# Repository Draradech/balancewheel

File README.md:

# Balance Wheel (Rev. 2)

This repository will grow over time to include everything you need to build your own balance wheel: 
https://hackaday.io/project/4267-balance-wheel

This includes circuit board design, partslist, drawings to lasercut HDF parts and build instructions.

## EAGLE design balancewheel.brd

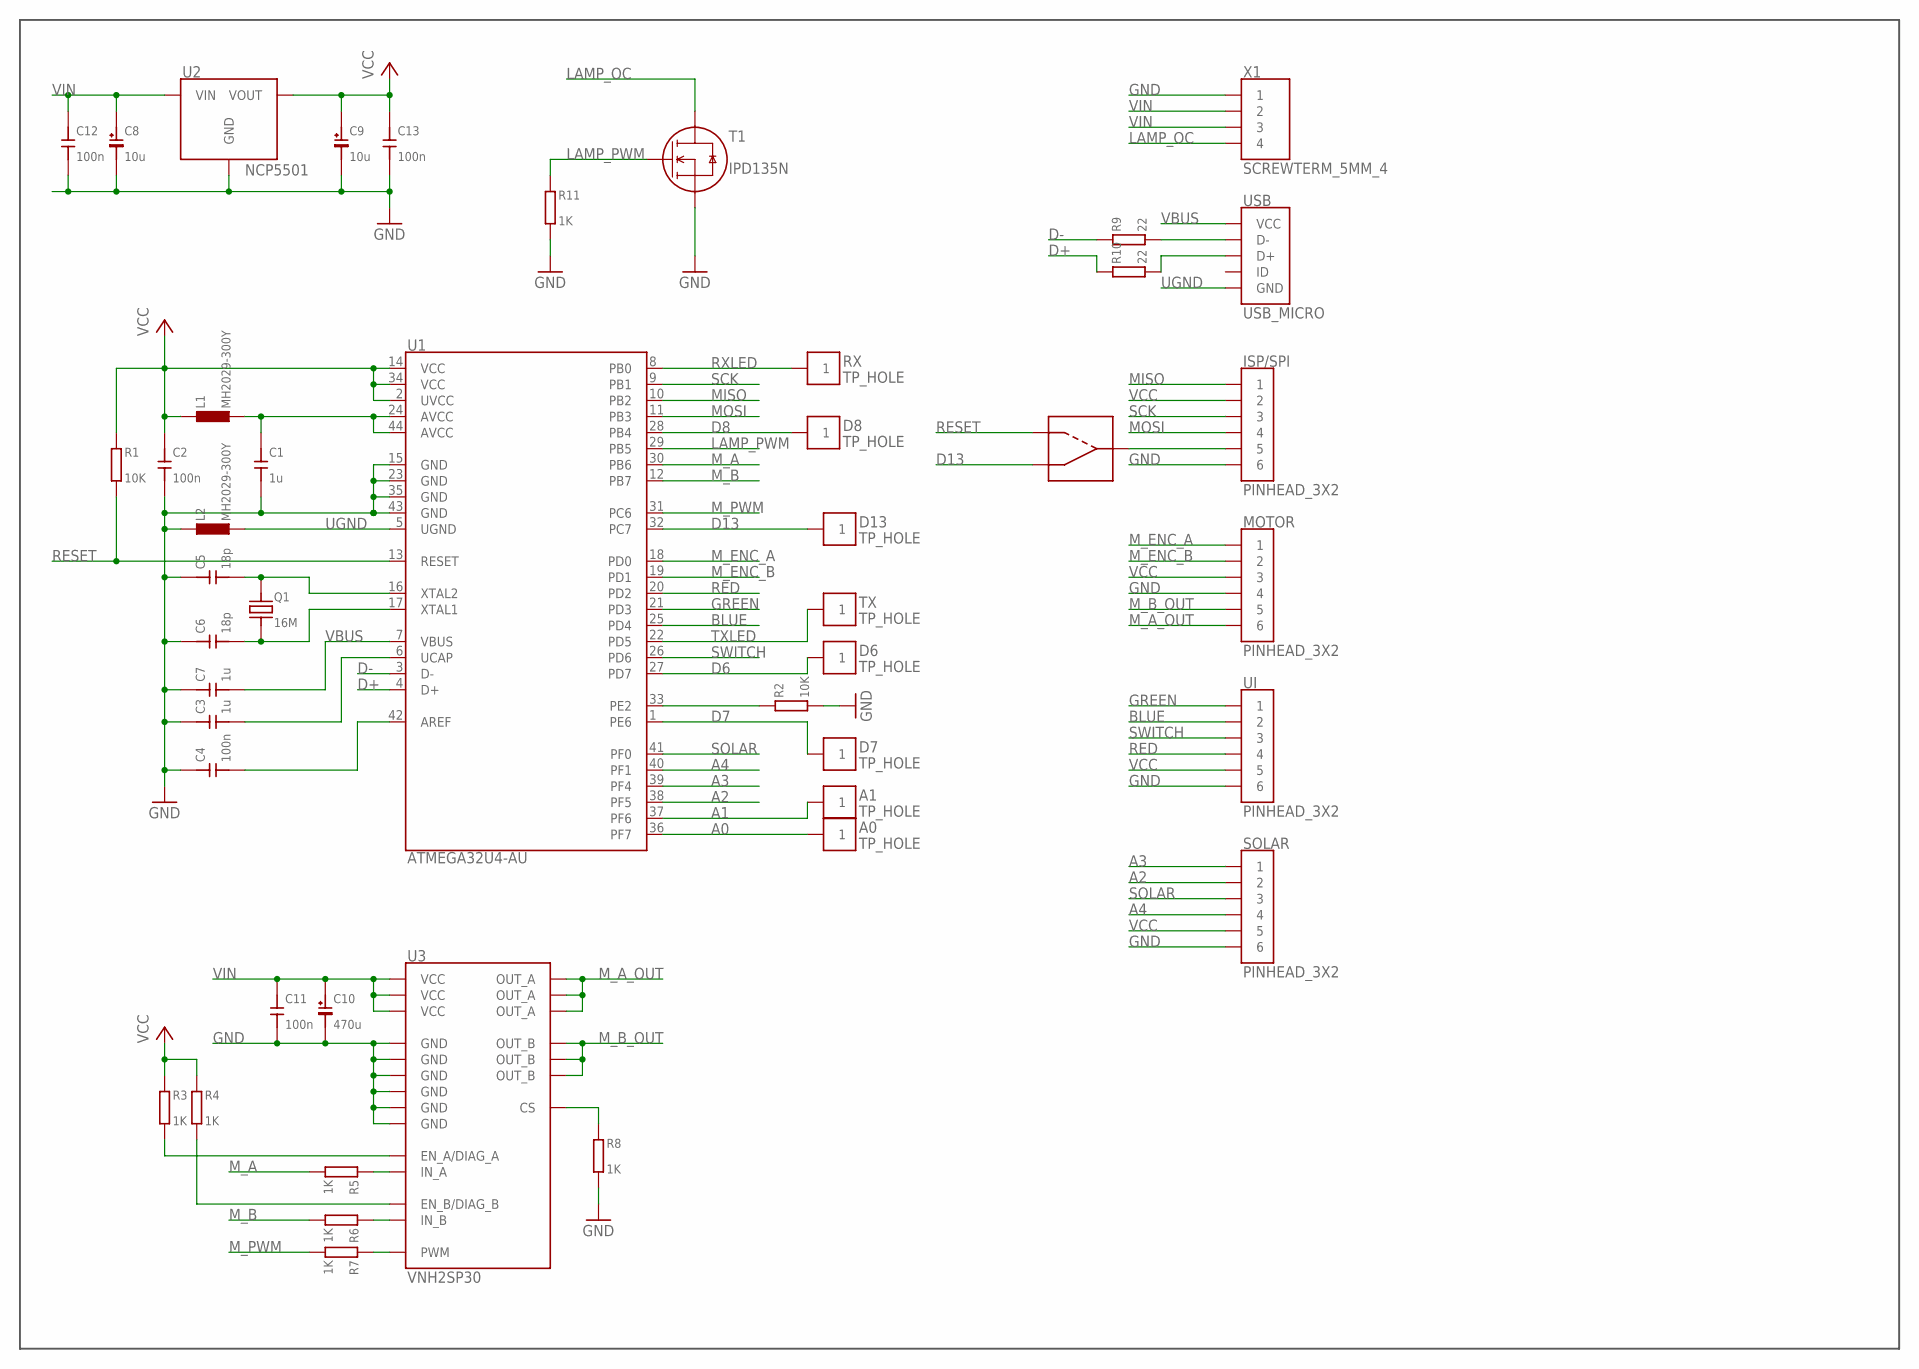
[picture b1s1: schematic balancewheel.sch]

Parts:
A0, A1: TP_HOLE; X1
C1, C3, C7: 1u; 0805
C2, C4, C11, C12, C13: 100n; 0805
C5, C6: 18p; 0805
C8, C9: 10u; CPOL_C
C10: 470u; CPOL_10
D6, D7, D8, D13: TP_HOLE; X1
ISP/SPI: PINHEAD_3X2; 3X2
L1, L2: MH2029-300Y; 0805
MOTOR: PINHEAD_3X2; 3X2
Q1: 16M; Q5X32
R1, R2: 10K; 0805
R3, R4, R5, R6, R7, R8, R11: 1K; 0805
R9, R10: 22; 0805
RX: TP_HOLE; X1
SJ1: SJ; X3
SOLAR: PINHEAD_3X2; 3X2
T1: IPD135N; DPAK
TX: TP_HOLE; X1
U1: ATMEGA32U4-AU; TQFP44
U2: NCP5501; DPAK
U3: VNH2SP30; MULTIPOWER30
UI: PINHEAD_3X2; 3X2
USB: USB_MICRO; MUSB
X1: SCREWTERM_5MM_4; 5MMSCREWTERMX4

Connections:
A0: A0.P$1, U1.36 (PF7)
A1: A1.P$1, U1.37 (PF6)
A2: SOLAR.2, U1.38 (PF5)
A3: SOLAR.1, U1.39 (PF4)
A4: SOLAR.4, U1.40 (PF1)
BLUE: U1.25 (PD4), UI.2
D6: D6.P$1, U1.27 (PD7)
D7: D7.P$1, U1.1 (PE6)
D8: D8.P$1, U1.28 (PB4)
D13: D13.P$1, SJ1.1, U1.32 (PC7)
D+: R10.P$2, U1.4 (D+)
D-: R9.P$2, U1.3 (D-)
GND: C1.P$1, C2.P$1, C3.P$2, C4.P$2, C5.P$2, C6.P$2, C7.P$2, C8.NEG, C9.NEG, C10.NEG, C11.P$1, C12.P$1, C13.P$1, ISP/SPI.6, L2.P$2, MOTOR.4, R2.P$1, R8.P$1, R11.P$1, SOLAR.6, T1.3 (S), U1.15 (GND), U1.23 (GND), U1.35 (GND), U1.43 (GND), U2.TAB (GND), U3.P$18 (GND), U3.P$19 (GND), U3.P$20 (GND), U3.P$26 (GND), U3.P$27 (GND), U3.P$28 (GND), UI.6, X1.1
GREEN: U1.21 (PD3), UI.1
LAMP_OC: T1.TAB (D), X1.4
LAMP_PWM: R11.P$2, T1.1 (G), U1.29 (PB5)
MISO: ISP/SPI.1, U1.10 (PB2)
MOSI: ISP/SPI.4, U1.11 (PB3)
M_A: R5.P$1, U1.30 (PB6)
M_A_OUT: MOTOR.6, U3.P$1 (OUT_A), U3.P$25 (OUT_A), U3.P$30 (OUT_A)
M_B: R6.P$1, U1.12 (PB7)
M_B_OUT: MOTOR.5, U3.P$15 (OUT_B), U3.P$16 (OUT_B), U3.P$21 (OUT_B)
M_ENC_A: MOTOR.1, U1.18 (PD0)
M_ENC_B: MOTOR.2, U1.19 (PD1)
M_PWM: R7.P$1, U1.31 (PC6)
unnamed: C1.P$2, L1.P$1, U1.24 (AVCC), U1.44 (AVCC)
unnamed: C3.P$1, U1.6 (UCAP)
unnamed: C4.P$1, U1.42 (AREF)
unnamed: C5.P$1, Q1.P$2, U1.16 (XTAL2)
unnamed: C6.P$1, Q1.P$1, U1.17 (XTAL1)
unnamed: R2.P$2, U1.33 (PE2)
unnamed: R8.P$2, U3.P$9 (CS)
unnamed: R9.P$1, USB.2 (D-)
unnamed: R10.P$1, USB.3 (D+)
unnamed: R3.P$1, U3.P$6 (EN_A/DIAG_A)
unnamed: R4.P$1, U3.P$10 (EN_B/DIAG_B)
unnamed: R5.P$2, U3.P$5 (IN_A)
unnamed: R6.P$2, U3.P$11 (IN_B)
unnamed: R7.P$2, U3.P$8 (PWM)
unnamed: ISP/SPI.5, SJ1.2
RED: U1.20 (PD2), UI.4
RESET: R1.P$1, SJ1.3, U1.13 (RESET)
RXLED: RX.P$1, U1.8 (PB0)
SCK: ISP/SPI.3, U1.9 (PB1)
SOLAR: SOLAR.3, U1.41 (PF0)
SWITCH: U1.26 (PD6), UI.3
TXLED: TX.P$1, U1.22 (PD5)
UGND: L2.P$1, U1.5 (UGND), USB.5 (GND)
VBUS: C7.P$1, U1.7 (VBUS), USB.1 (VCC)
VCC: C2.P$2, C9.POS, C13.P$2, ISP/SPI.2, L1.P$2, MOTOR.3, R1.P$2, R3.P$2, R4.P$2, SOLAR.5, U1.2 (UVCC), U1.14 (VCC), U1.34 (VCC), U2.3 (VOUT), UI.5
VIN: C8.POS, C10.POS, C11.P$2, C12.P$2, U2.1 (VIN), U3.P$3 (VCC), U3.P$13 (VCC), U3.P$23 (VCC), X1.2, X1.3

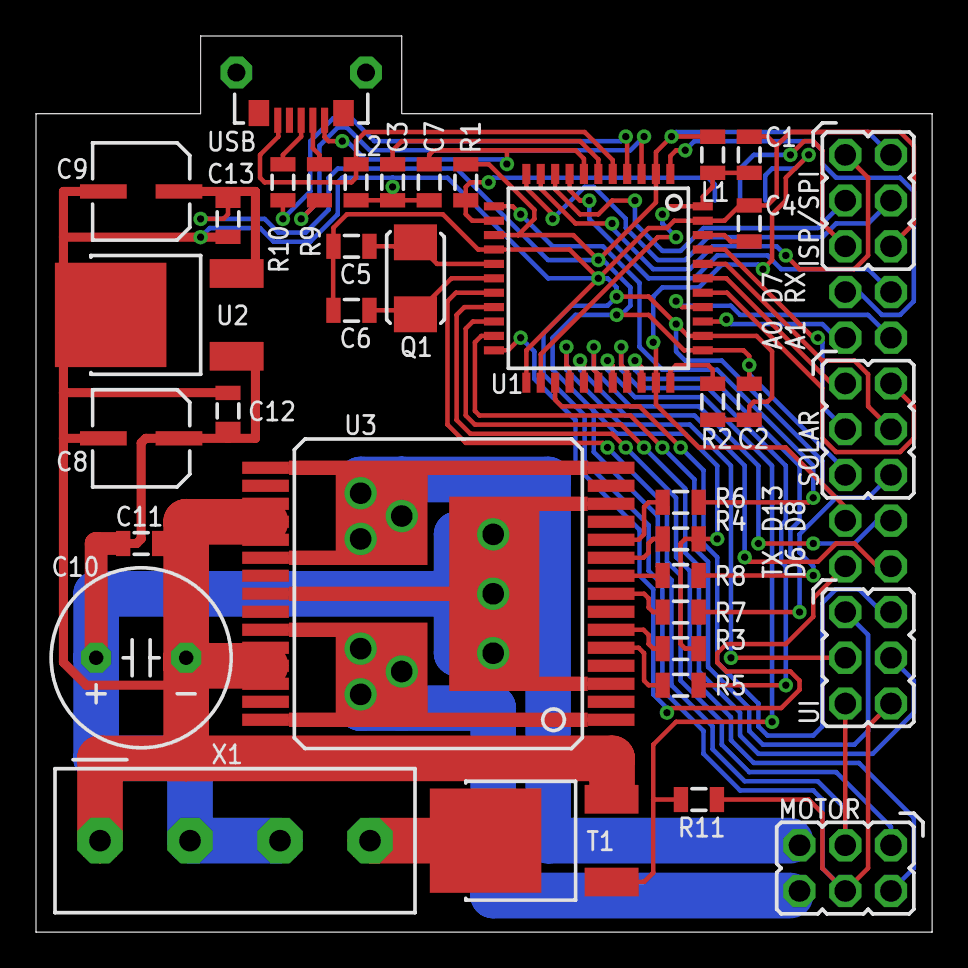
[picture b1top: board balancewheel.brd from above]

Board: 2 copper layers, 49.8 x 49.8 mm, 46 parts (1 on the bottom side), 51 nets.

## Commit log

2015-02-15 moved pcb layout to subfolder
